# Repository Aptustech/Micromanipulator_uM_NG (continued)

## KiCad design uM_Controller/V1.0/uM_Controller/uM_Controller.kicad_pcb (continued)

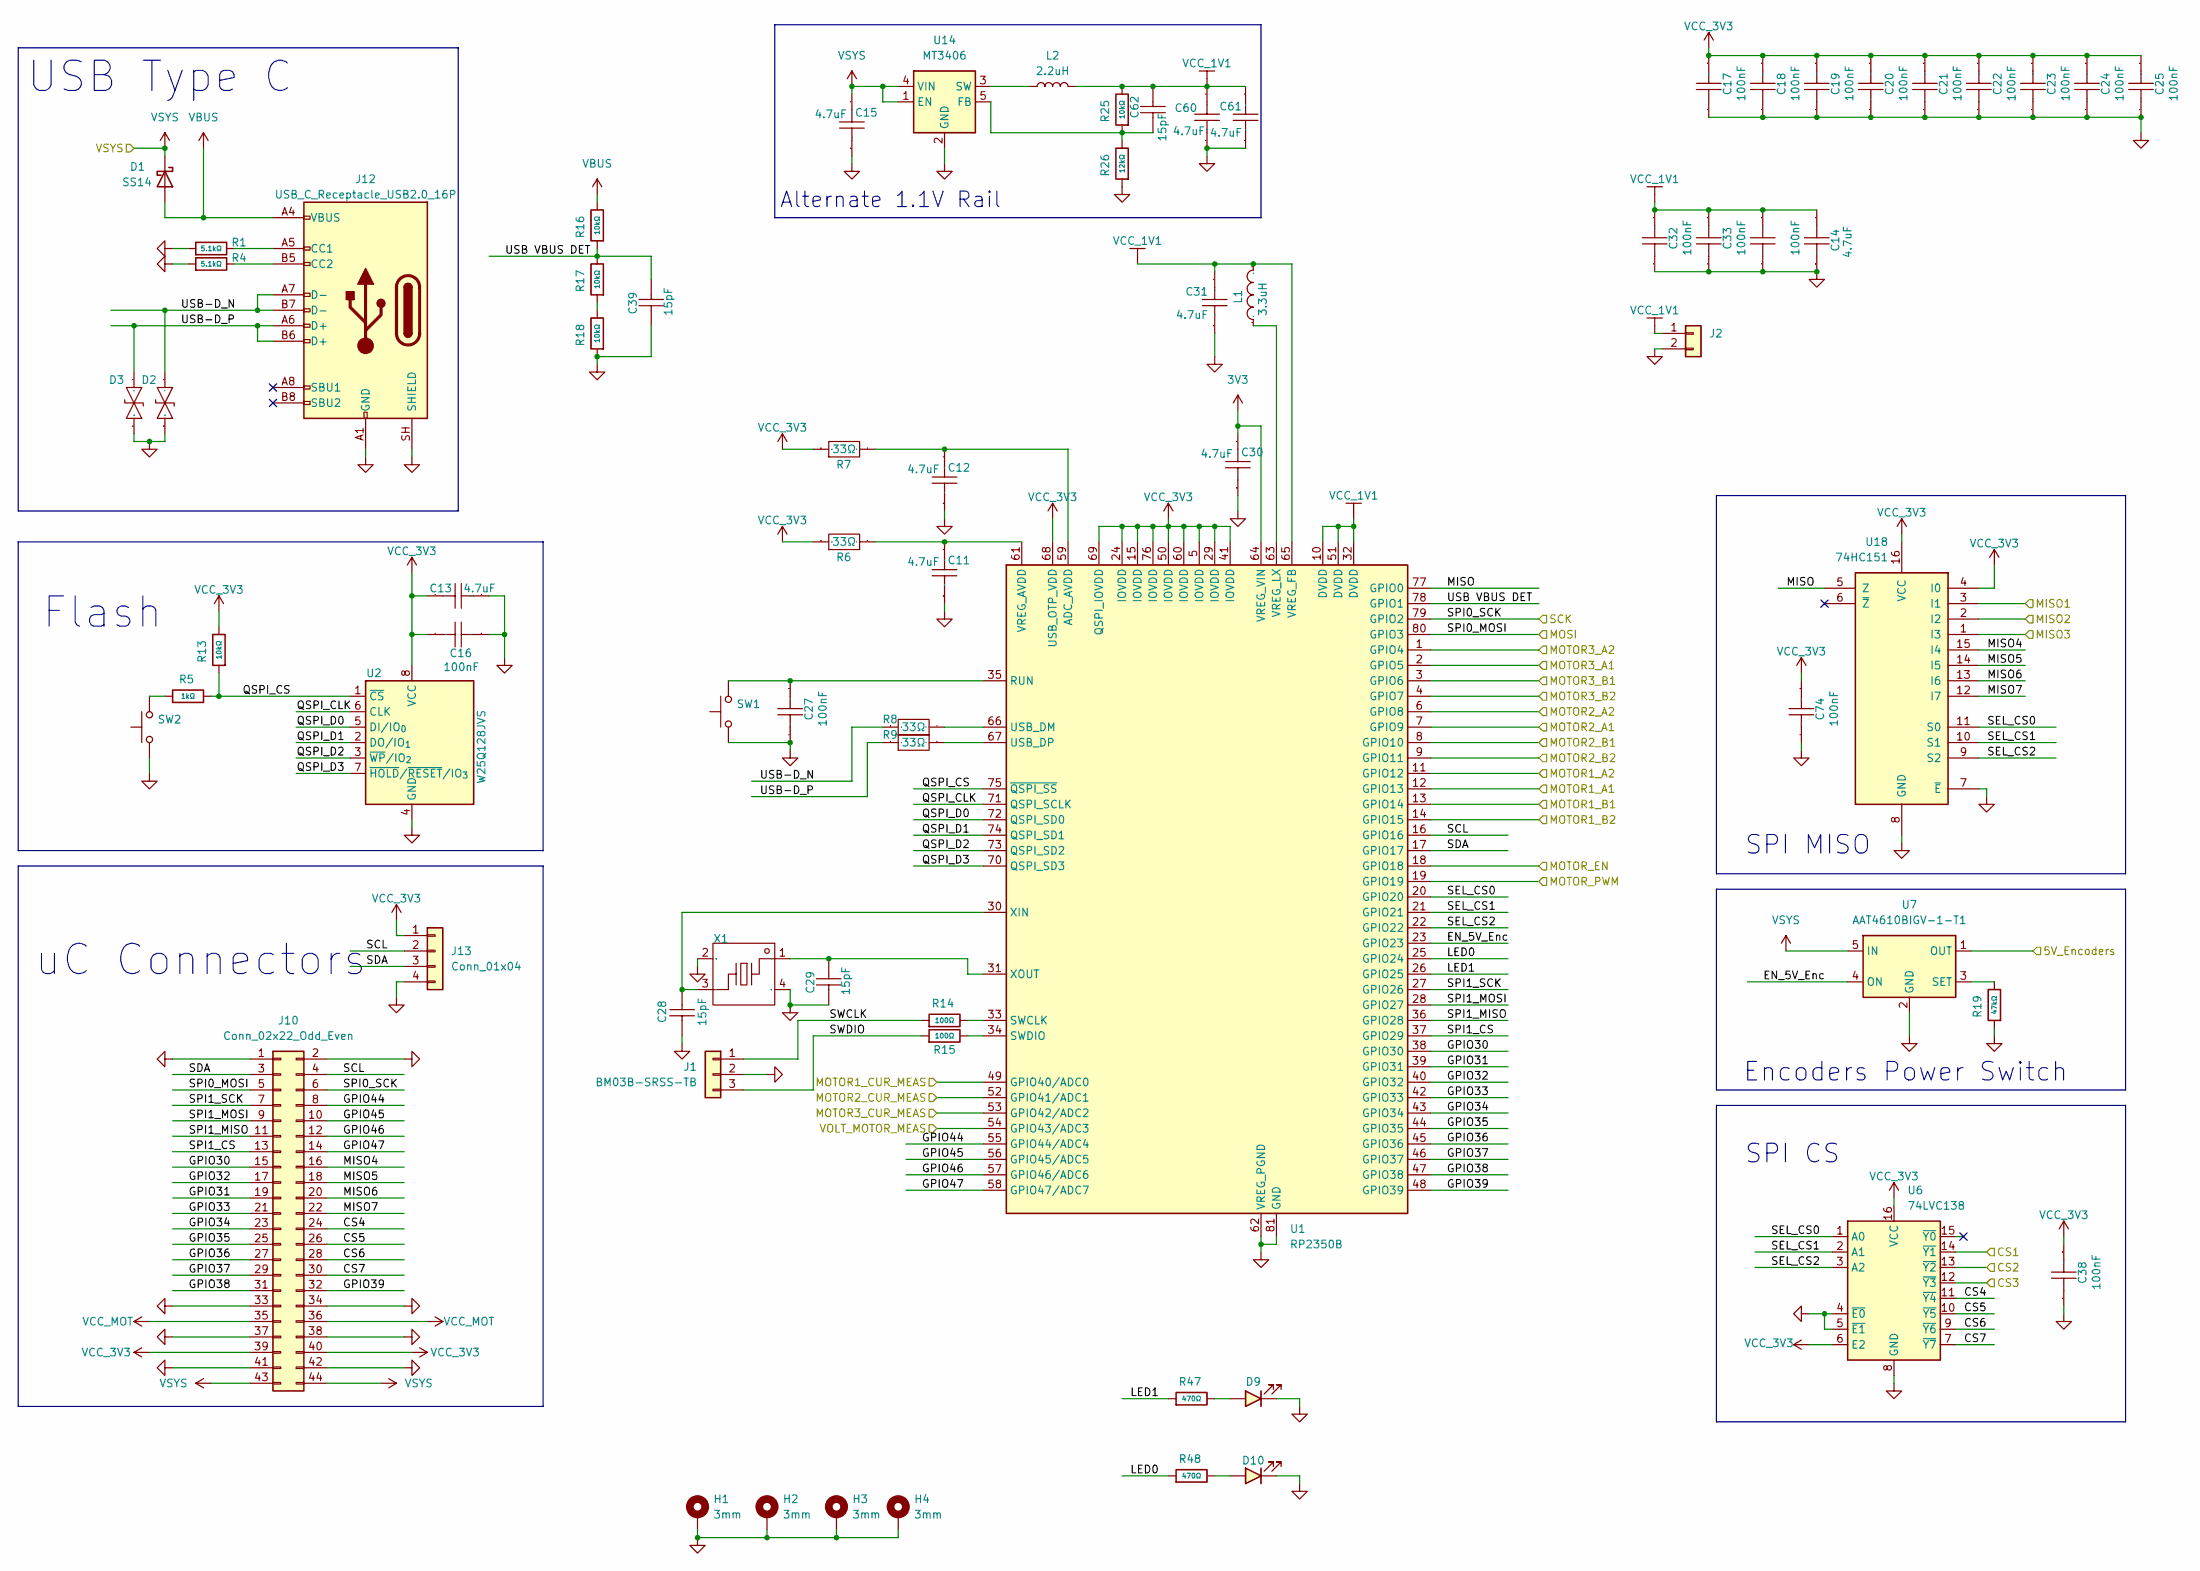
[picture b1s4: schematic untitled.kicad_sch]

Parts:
C11, C12, C13, C14, C15, C60, C61: 4.7uF; C_0402_1005Metric; Manufacturer Part CL05A475MP5NRNC; LCSC Part Name 4.7uF ±20% 10V
C16, C17, C18, C19, C20, C21, C22, C23, C24, C25, C27, C32, C33, C34, C38, C74: 100nF; C_0402_1005Metric; Manufacturer Part CL05B104KO5NNNC; LCSC Part Name 100nF ±10% 16V
C28, C29, C39, C62: 15pF; C_0402_1005Metric; Manufacturer Part 0402CG150J500NT; LCSC Part Name 15pF ±5% 50V
C30, C31: 4.7uF; C_0603_1608Metric; Manufacturer Part CL10A475KO8NNNC; LCSC Part Name 16V 4.7uF X5R ±10% 0603
D1: SS14; D_SMA; Manufacturer Part SS14; LCSC C2480
D2, D3: RCLAMP0521P.TCT-MS; D_0402_1005Metric; Manufacturer Part RCLAMP0521P.TCT-MS; LCSC Part Name 双向TVS 5V截止 4A峰值脉冲 丝印N
D9: LED; LED_0805_2012Metric; Manufacturer Part KT-0805G; LCSC C2297
D10: LED; LED_0805_2012Metric; Manufacturer Part NCD0805R1; LCSC C84256
H1, H2, H3, H4: 3mm; MountingHole_3.2mm_M3_ISO14580_Pad_TopBottom
J1: BM03B-SRSS-TB; JST_SH_BM03B-SRSS-TB_1x03-1MP_P1.00mm_Vertical; Manufacturer Part BM03B-SRSS-TB; LCSC C160389
J2: Conn_01x02; PinHeader_1x02_P2.54mm_Vertical
J10: Conn_02x22_Odd_Even; PinHeader_2x22_P2.54mm_Vertical
J12: USB_C_Receptacle_USB2.0_16P; USB_C_Receptacle_GCT_USB4105-xx-A_16P_TopMnt_Horizontal; Manufacturer Part USB4105-GF-A-120; LCSC C5184243
J13: Conn_01x04; PinHeader_1x04_P2.54mm_Vertical
L1: L_Changjiang_FTC201610D; Manufacturer Part AOTA-B201610S3R3-101-T; LCSC Part Name AOTA-B201610S3R3-101-T
L2: 2.2uH; L_1008_2520Metric; Manufacturer Part FTC252010S2R2MBCA; LCSC C5832358
R1, R4: 5.1kΩ; R_0402_1005Metric; Overload Voltage (Max) 50V; Tolerance ±1%; Part 0402WGF5101TCE; LCSC C25905
R5: 1kΩ; R_0402_1005Metric; Overload Voltage (Max) 50V; Tolerance ±1%; Part 0402WGF1001TCE; LCSC C11702
R6, R7, R8, R9: 33Ω; R_0402_1005Metric; Manufacturer Part 0402WGF330JTCE; LCSC Part Name 33Ω ±1% 62.5mW 厚膜电阻
R13, R16, R17, R18, R25: 10kΩ; R_0402_1005Metric; Overload Voltage (Max) 50V; Tolerance ±1%; Part 0402WGF1002TCE; LCSC C25744
R14, R15: 100Ω; R_0402_1005Metric; Overload Voltage (Max) 50V; Tolerance ±1%; Part 0402WGF1000TCE; LCSC C25076
R19: 47kΩ; R_0402_1005Metric; Overload Voltage (Max) 50V; Tolerance ±1%; Part 0402WGF4702TCE; LCSC C25792
R26: 12kΩ; R_0402_1005Metric; Overload Voltage (Max) 50V; Tolerance ±1%; Part 0402WGF1202TCE; LCSC C25752
R47, R48: 470Ω; R_0402_1005Metric; Overload Voltage (Max) 50V; Tolerance ±1%; Part 0402WGF4700TCE; LCSC C25117
SW1, SW2: K2-1808SN-A4SW-01; SW_Push_1P1T_XKB_TS-1187A; Manufacturer Part TS-1187A-B-A-B; LCSC C318884
U1: RP2350B; QFN-80-1EP_10x10mm_P0.4mm_EP3.4x3.4mm
U2: W25Q128JVS; SOIC-8_5.3x5.3mm_P1.27mm
U6: 74LVC138; TSSOP-16_4.4x5mm_P0.65mm; Manufacturer Part AiP74LVC138TA16.TB; LCSC C5361835
U7: AAT4610BIGV-1-T1; SOT-23-5; Manufacturer Part RY2121; LCSC C2887853
U14: MT3406; SOT-23-5; Manufacturer Part MT3406; LCSC C22462728
U18: 74HC151; TSSOP-16_4.4x5mm_P0.65mm; Manufacturer Part MC74HC151ADTR2G; LCSC C152523
X1: Crystal_SMD_3225-4Pin_3.2x2.5mm; Manufacturer Part YXC Crystal Oscillators; LCSC C9002

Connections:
3V3: C30.2, U1.64 (VREG_VIN)
/Motors/MOTOR1_A1: U1.12 (GPIO13); also elsewhere on the board
/Motors/MOTOR1_A2: U1.11 (GPIO12); also elsewhere on the board
/Motors/MOTOR1_B1: U1.13 (GPIO14); also elsewhere on the board
/Motors/MOTOR1_B2: U1.14 (GPIO15); also elsewhere on the board
/Motors/MOTOR1_CUR_MEAS: U1.49 (GPIO40/ADC0); also elsewhere on the board
/Motors/MOTOR2_A1: U1.7 (GPIO9); also elsewhere on the board
/Motors/MOTOR2_A2: U1.6 (GPIO8); also elsewhere on the board
/Motors/MOTOR2_B1: U1.8 (GPIO10); also elsewhere on the board
/Motors/MOTOR2_B2: U1.9 (GPIO11); also elsewhere on the board
/Motors/MOTOR2_CUR_MEAS: U1.52 (GPIO41/ADC1); also elsewhere on the board
/Motors/MOTOR3_A1: U1.2 (GPIO5); also elsewhere on the board
/Motors/MOTOR3_A2: U1.1 (GPIO4); also elsewhere on the board
/Motors/MOTOR3_B1: U1.3 (GPIO6); also elsewhere on the board
/Motors/MOTOR3_B2: U1.4 (GPIO7); also elsewhere on the board
/Motors/MOTOR3_CUR_MEAS: U1.53 (GPIO42/ADC2); also elsewhere on the board
/Motors/MOTOR_EN: U1.18 (GPIO18); also elsewhere on the board
/Motors/MOTOR_PWM: U1.19 (GPIO19); also elsewhere on the board
/Motors/VOLT_MOTOR_MEAS: U1.54 (GPIO43/ADC3); also elsewhere on the board
/RP2350B/CS1: U6.14 (~Y1); also elsewhere on the board
/RP2350B/CS2: U6.13 (~Y2); also elsewhere on the board
/RP2350B/CS3: U6.12 (~Y3); also elsewhere on the board
/RP2350B/CS4: J10.24, U6.11 (~Y4)
/RP2350B/CS5: J10.26, U6.10 (~Y5)
/RP2350B/CS6: J10.28, U6.9 (~Y6)
/RP2350B/CS7: J10.30, U6.7 (~Y7)
/RP2350B/EN_5V_Enc: U1.23 (GPIO23), U7.4 (ON)
/RP2350B/GPIO30: J10.15, U1.38 (GPIO30)
/RP2350B/GPIO31: J10.19, U1.39 (GPIO31)
/RP2350B/GPIO32: J10.17, U1.40 (GPIO32)
/RP2350B/GPIO33: J10.21, U1.42 (GPIO33)
/RP2350B/GPIO34: J10.23, U1.43 (GPIO34)
/RP2350B/GPIO35: J10.25, U1.44 (GPIO35)
/RP2350B/GPIO36: J10.27, U1.45 (GPIO36)
/RP2350B/GPIO37: J10.29, U1.46 (GPIO37)
/RP2350B/GPIO38: J10.31, U1.47 (GPIO38)
/RP2350B/GPIO39: J10.32, U1.48 (GPIO39)
/RP2350B/GPIO44: J10.8, U1.55 (GPIO44/ADC4)
/RP2350B/GPIO45: J10.10, U1.56 (GPIO45/ADC5)
/RP2350B/GPIO46: J10.12, U1.57 (GPIO46/ADC6)
/RP2350B/GPIO47: J10.14, U1.58 (GPIO47/ADC7)
/RP2350B/LED0: R48.1, U1.25 (GPIO24)
/RP2350B/LED1: R47.1, U1.26 (GPIO25)
/RP2350B/MISO: U1.77 (GPIO0), U18.5 (Z)
/RP2350B/MISO1: U18.3 (I1); also elsewhere on the board
/RP2350B/MISO2: U18.2 (I2); also elsewhere on the board
/RP2350B/MISO3: U18.1 (I3); also elsewhere on the board
/RP2350B/MISO4: J10.16, U18.15 (I4)
/RP2350B/MISO5: J10.18, U18.14 (I5)
/RP2350B/MISO6: J10.20, U18.13 (I6)
/RP2350B/MISO7: J10.22, U18.12 (I7)
/RP2350B/QSPI_CLK: U1.71 (QSPI_SCLK), U2.6 (CLK)
/RP2350B/QSPI_CS: R5.2, R13.1, U1.75 (~QSPI_SS), U2.1 (~CS)
/RP2350B/QSPI_D0: U1.72 (QSPI_SD0), U2.5 (DI/IO_{0})
/RP2350B/QSPI_D1: U1.74 (QSPI_SD1), U2.2 (DO/IO_{1})
/RP2350B/QSPI_D2: U1.73 (QSPI_SD2), U2.3 (~WP/IO_{2})
/RP2350B/QSPI_D3: U1.70 (QSPI_SD3), U2.7 (~HOLD/~RESET/IO_{3})
/RP2350B/SCL: J10.4, J13.2, U1.16 (GPIO16)
/RP2350B/SDA: J10.3, J13.3, U1.17 (GPIO17)
/RP2350B/SEL_CS0: U1.20 (GPIO20), U6.1 (A0), U18.11 (S0)
/RP2350B/SEL_CS1: U1.21 (GPIO21), U6.2 (A1), U18.10 (S1)
/RP2350B/SEL_CS2: U1.22 (GPIO22), U6.3 (A2), U18.9 (S2)
/RP2350B/SPI0_MOSI: J10.5, U1.80 (GPIO3); also elsewhere on the board
/RP2350B/SPI0_SCK: J10.6, U1.79 (GPIO2); also elsewhere on the board
/RP2350B/SPI1_CS: J10.13, U1.37 (GPIO29)
/RP2350B/SPI1_MISO: J10.11, U1.36 (GPIO28)
/RP2350B/SPI1_MOSI: J10.9, U1.28 (GPIO27)
/RP2350B/SPI1_SCK: J10.7, U1.27 (GPIO26)
/RP2350B/SWCLK: J1.1, R14.1
/RP2350B/SWDIO: J1.3, R15.1
/RP2350B/USB VBUS DET: C39.1, R16.1, R17.2, U1.78 (GPIO1)
/RP2350B/USB-D_N: D2.2, J12.A7 (D-), J12.B7 (D-), R8.1
/RP2350B/USB-D_P: D3.2, J12.A6 (D+), J12.B6 (D+), R9.1
/SPI_Encoders/VCC_5V_Encoders: U7.1 (OUT); also elsewhere on the board
GND: C11.1, C12.1, C13.1, C14.1, C15.1, C16.1, C17.2, C18.2, C19.2, C20.2, C21.2, C22.2, C23.2, C24.2, C25.2, C27.2, C28.2, C29.2, C30.1, C31.1, C32.2, C33.2, C34.2, C38.2, C39.2, C60.1, C61.1, C74.2, D2.1, D3.1, D9.1 (K), D10.1 (K), H1.1 (1_1), H2.1 (1_1), H3.1 (1_1), H4.1 (1_1), J1.2, J2.2, J10.1, J10.2, J10.33, J10.34, J10.37, J10.38, J10.41, J10.42, J12.A1 (GND), J12.A12 (GND), J12.B1 (GND), J12.B12 (GND), J12.SH (SHIELD), J13.4, R1.1, R4.1, R18.1, R19.1, R26.1, SW1.1, SW2.1, U1.62 (VREG_PGND), U1.81 (GND), U2.4 (GND), U6.4 (~E0), U6.5 (~E1), U6.8 (GND), U7.2 (GND), U14.2 (GND), U18.7 (~E), U18.8 (GND), X1.2 (GND), X1.4 (GND); also elsewhere on the board
unnamed: D9.2 (A), R47.2
unnamed: D10.2 (A), R48.2
unnamed: J12.A5 (CC1), R1.2
unnamed: J12.B5 (CC2), R4.2
unnamed: R5.1, SW2.2
unnamed: R17.1, R18.2
unnamed: C12.2, R7.2, U1.59 (ADC_AVDD)
unnamed: C27.1, SW1.2, U1.35 (RUN)
unnamed: R14.2, U1.33 (SWCLK)
unnamed: R15.2, U1.34 (SWDIO)
unnamed: R8.2, U1.66 (USB_DM)
unnamed: R9.2, U1.67 (USB_DP)
unnamed: C11.2, R6.2, U1.61 (VREG_AVDD)
unnamed: L1.1, U1.63 (VREG_LX)
unnamed: C28.1, U1.30 (XIN), X1.3
unnamed: C29.1, U1.31 (XOUT), X1.1
unnamed: R19.2, U7.3 (SET)
unnamed: C62.2, R25.1, R26.2, U14.5 (FB)
unnamed: L2.1, U14.3 (SW)
VBUS: D1.2 (A), J12.A4 (VBUS), J12.A9 (VBUS), J12.B4 (VBUS), J12.B9 (VBUS), R16.2
VCC_1V1: C14.2, C31.2, C32.1, C33.1, C34.1, C60.2, C61.2, C62.1, J2.1, L1.2, L2.2, R25.2, U1.10 (DVDD), U1.32 (DVDD), U1.51 (DVDD), U1.65 (VREG_FB)
VCC_3V3: C13.2, C16.2, C17.1, C18.1, C19.1, C20.1, C21.1, C22.1, C23.1, C24.1, C25.1, C38.1, C74.1, J10.39, J10.40, J13.1, R6.1, R7.1, R13.2, U1.5 (IOVDD), U1.15 (IOVDD), U1.24 (IOVDD), U1.29 (IOVDD), U1.41 (IOVDD), U1.50 (IOVDD), U1.60 (IOVDD), U1.68 (USB_OTP_VDD), U1.69 (QSPI_IOVDD), U1.76 (IOVDD), U2.8 (VCC), U6.6 (E2), U6.16 (VCC), U18.4 (I0), U18.16 (VCC); also elsewhere on the board
VCC_MOT: J10.35, J10.36; also elsewhere on the board
VSYS: C15.2, D1.1 (K), J10.43, J10.44, U7.5 (IN), U14.1 (EN), U14.4 (VIN); also elsewhere on the board

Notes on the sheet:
Flash
SPI MISO
USB Type C
Encoders Power Switch
uC Connectors
SPI CS
Alternate 1.1V Rail

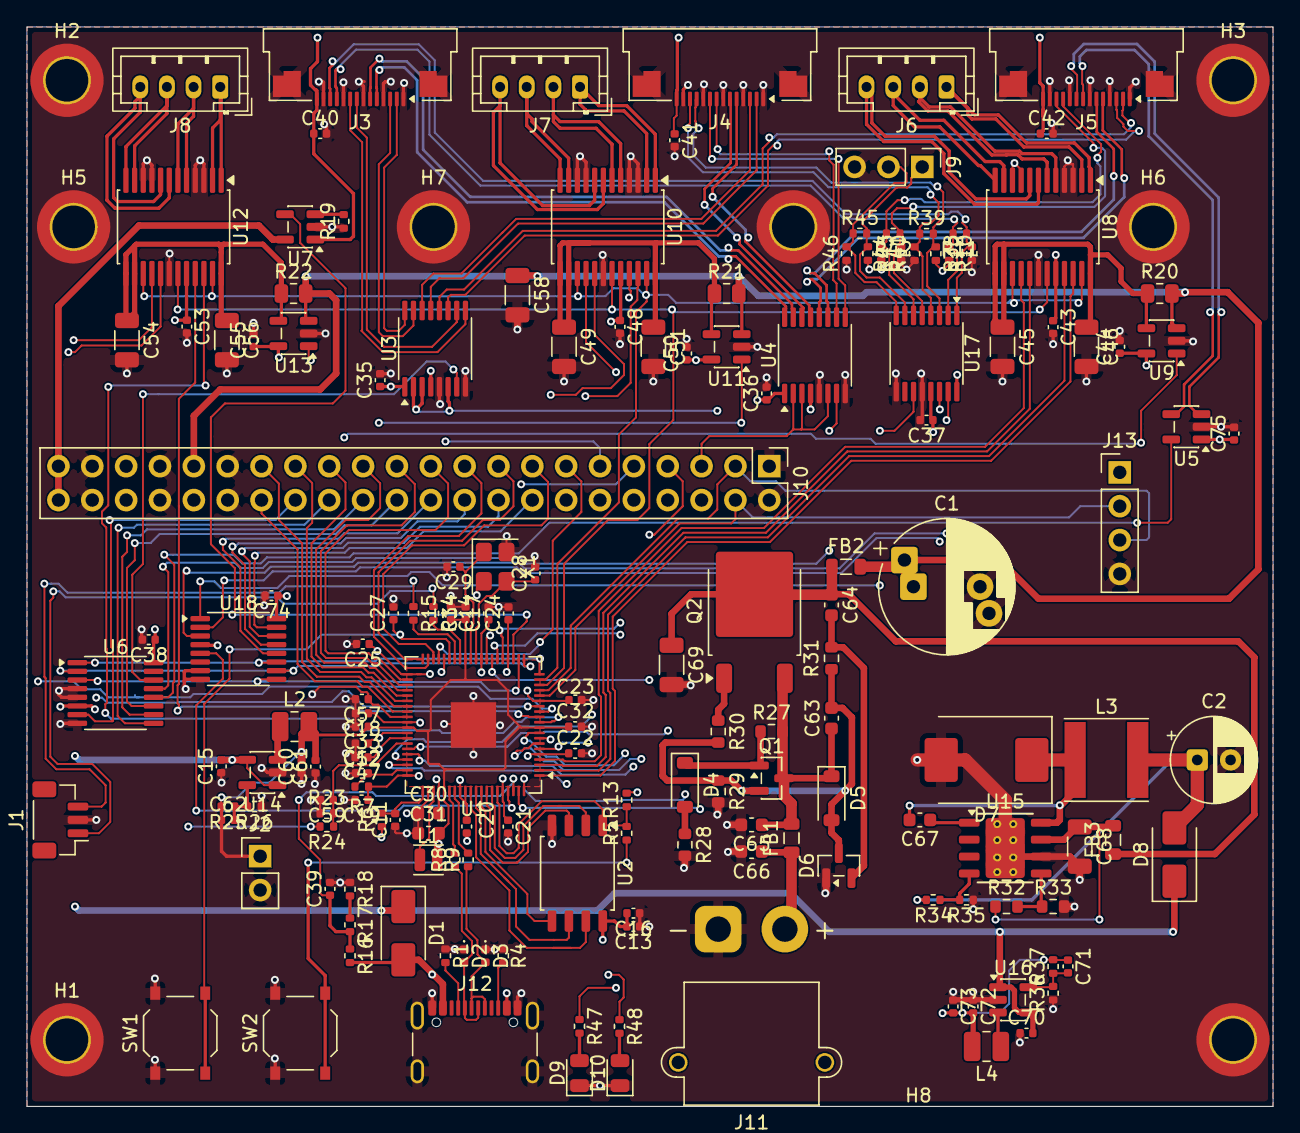
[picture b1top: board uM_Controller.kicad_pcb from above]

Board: 4 copper layers, 93.5 x 81.0 mm, 173 parts (0 on the bottom side), 156 nets.

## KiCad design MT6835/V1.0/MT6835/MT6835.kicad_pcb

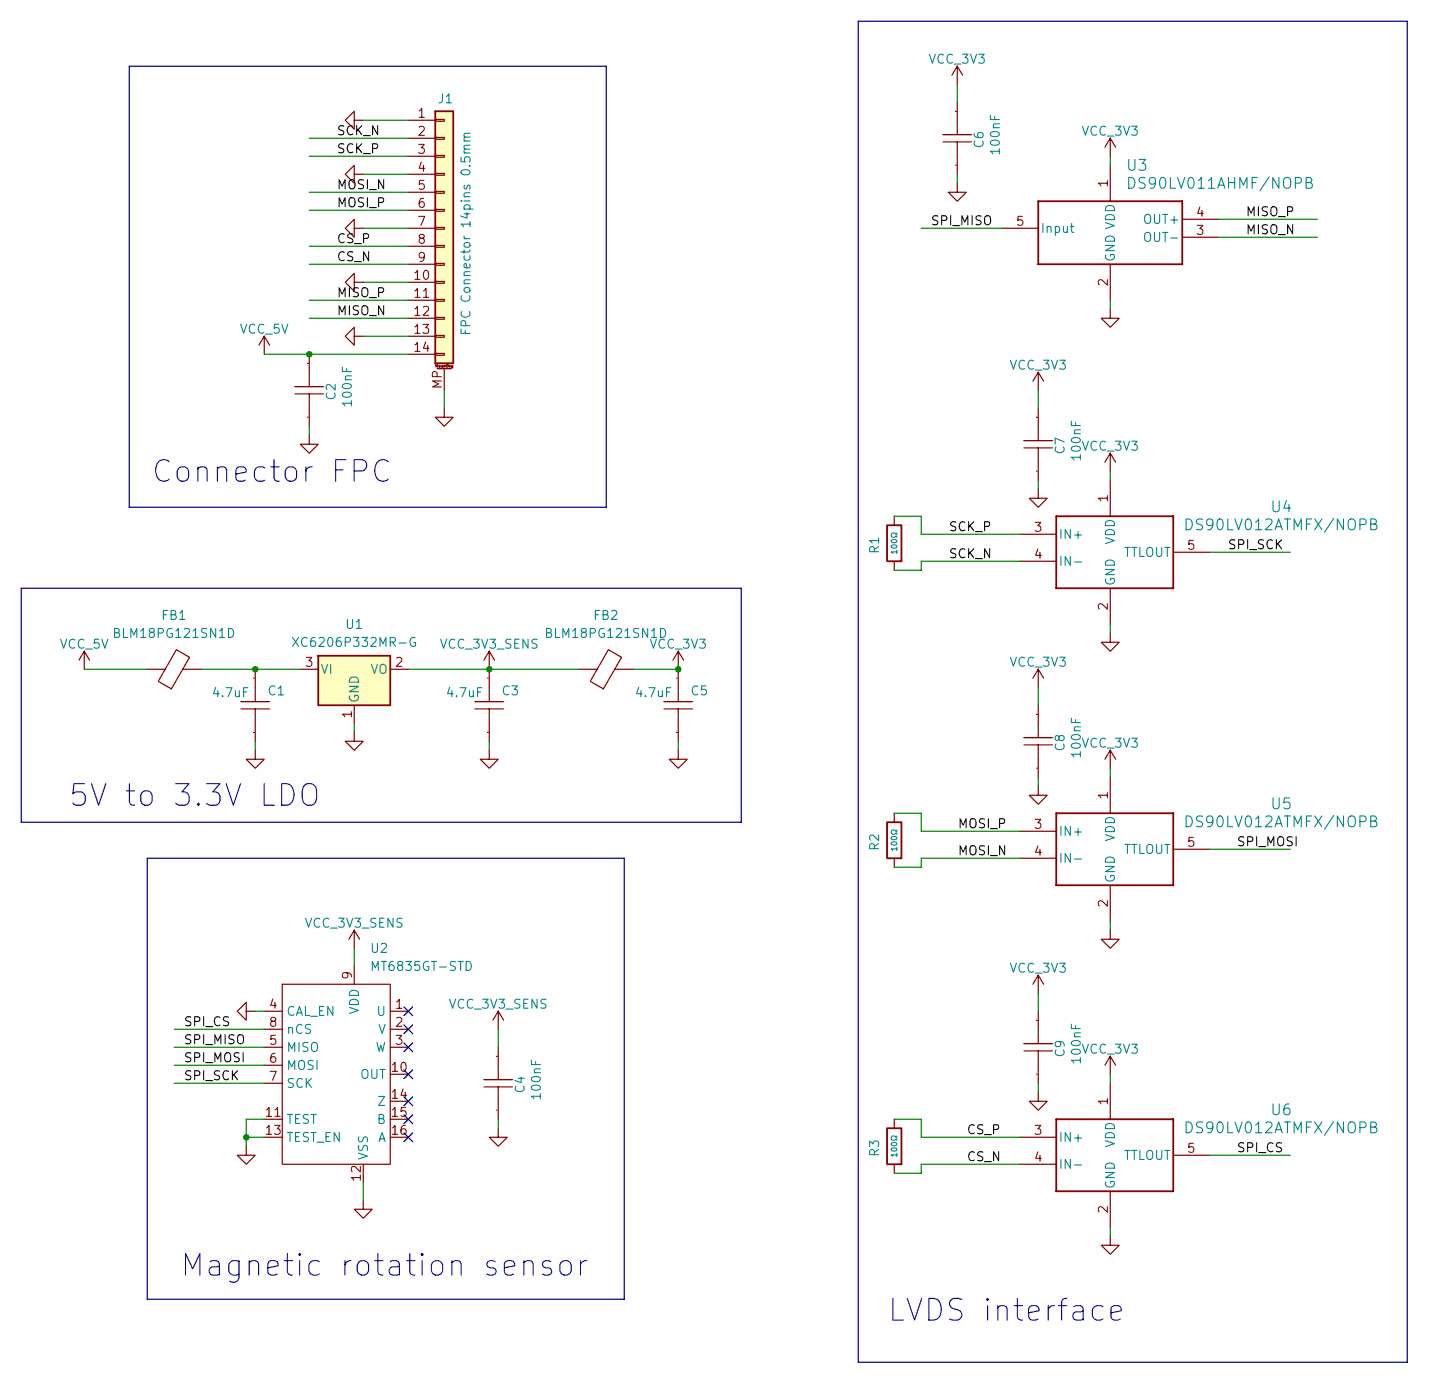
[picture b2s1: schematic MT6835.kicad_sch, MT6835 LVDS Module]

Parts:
C1, C3, C5: 4.7uF; C_0402_1005Metric; Manufacturer Part CL05A475MP5NRNC; LCSC Part Name 4.7uF ±20% 10V
C2, C4, C6, C7, C8, C9: 100nF; C_0402_1005Metric; Manufacturer Part CL05B104KO5NNNC; LCSC Part Name 100nF ±10% 16V
FB1, FB2: BLM18PG121SN1D; L_0603_1608Metric; Manufacturer Part BLM18PG121SN1D; LCSC C14709
J1: FPC Connector 14pins 0.5mm; Amphenol_F32R-1A7x1-11014_1x14-1MP_P0.5mm_Horizontal; Manufacturer Part F32R-1A7H1-11014 / AFC07-S14FCC-00; LCSC C38179
R1, R2, R3: 100Ω; R_0402_1005Metric; Overload Voltage (Max) 50V; Tolerance ±1%; Part 0402WGF1000TCE; LCSC C25076
U1: XC6206P332MR-G; SOT-23-3; Manufacturer Part XC6206P332MR-G; LCSC C5446
U2: MT6835GT-STD; TSSOP-16_4.4x5mm_P0.65mm; Manufacturer Part MT6835GT-STD-R; LCSC C2932578
U3: DS90LV011AHMF/NOPB; SOT-23-5; Manufacturer Part DS90LV011AHMF/NOPB; LCSC C2671548
U4, U5, U6: DS90LV012ATMFX/NOPB; SOT-23-5

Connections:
/CS_N: J1.9, R3.1, U6.4 (IN-)
/CS_P: J1.8, R3.2, U6.3 (IN+)
/MISO_N: J1.12, U3.3 (OUT-)
/MISO_P: J1.11, U3.4 (OUT+)
/MOSI_N: J1.5, R2.1, U5.4 (IN-)
/MOSI_P: J1.6, R2.2, U5.3 (IN+)
/SCK_N: J1.2, R1.1, U4.4 (IN-)
/SCK_P: J1.3, R1.2, U4.3 (IN+)
/SPI_CS: U2.8 (nCS), U6.5 (TTLOUT)
/SPI_MISO: U2.5 (MISO), U3.5 (Input)
/SPI_MOSI: U2.6 (MOSI), U5.5 (TTLOUT)
/SPI_SCK: U2.7 (SCK), U4.5 (TTLOUT)
GND: C1.1, C2.2, C3.1, C4.2, C5.1, C6.2, C7.2, C8.2, C9.2, J1.1, J1.4, J1.7, J1.10, J1.13, J1.MP (MountPin), U1.1 (GND), U2.4 (CAL_EN), U2.11 (TEST), U2.12 (VSS), U2.13 (TEST_EN), U3.2 (GND), U4.2 (GND), U5.2 (GND), U6.2 (GND)
unnamed: C1.2, FB1.2, U1.3 (VI)
VCC_3V3: C5.2, C6.1, C7.1, C8.1, C9.1, FB2.2, U3.1 (VDD), U4.1 (VDD), U5.1 (VDD), U6.1 (VDD)
VCC_3V3_SENS: C3.2, C4.1, FB2.1, U1.2 (VO), U2.9 (VDD)
VCC_5V: C2.1, FB1.1, J1.14

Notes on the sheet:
5V to 3.3V LDO
Magnetic rotation sensor
Connector FPC
LVDS interface

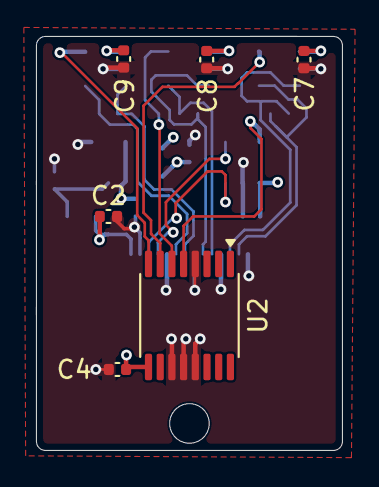
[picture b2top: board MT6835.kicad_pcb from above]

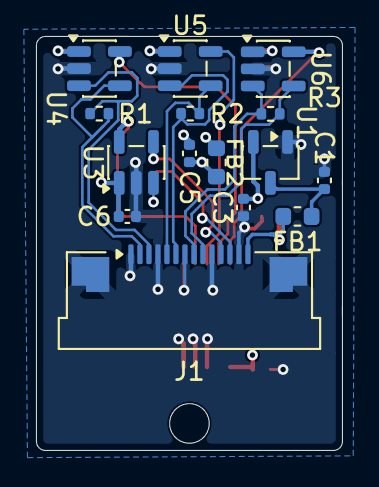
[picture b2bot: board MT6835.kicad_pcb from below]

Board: 4 copper layers, 17.0 x 23.0 mm, 21 parts (15 on the bottom side), 17 nets.
